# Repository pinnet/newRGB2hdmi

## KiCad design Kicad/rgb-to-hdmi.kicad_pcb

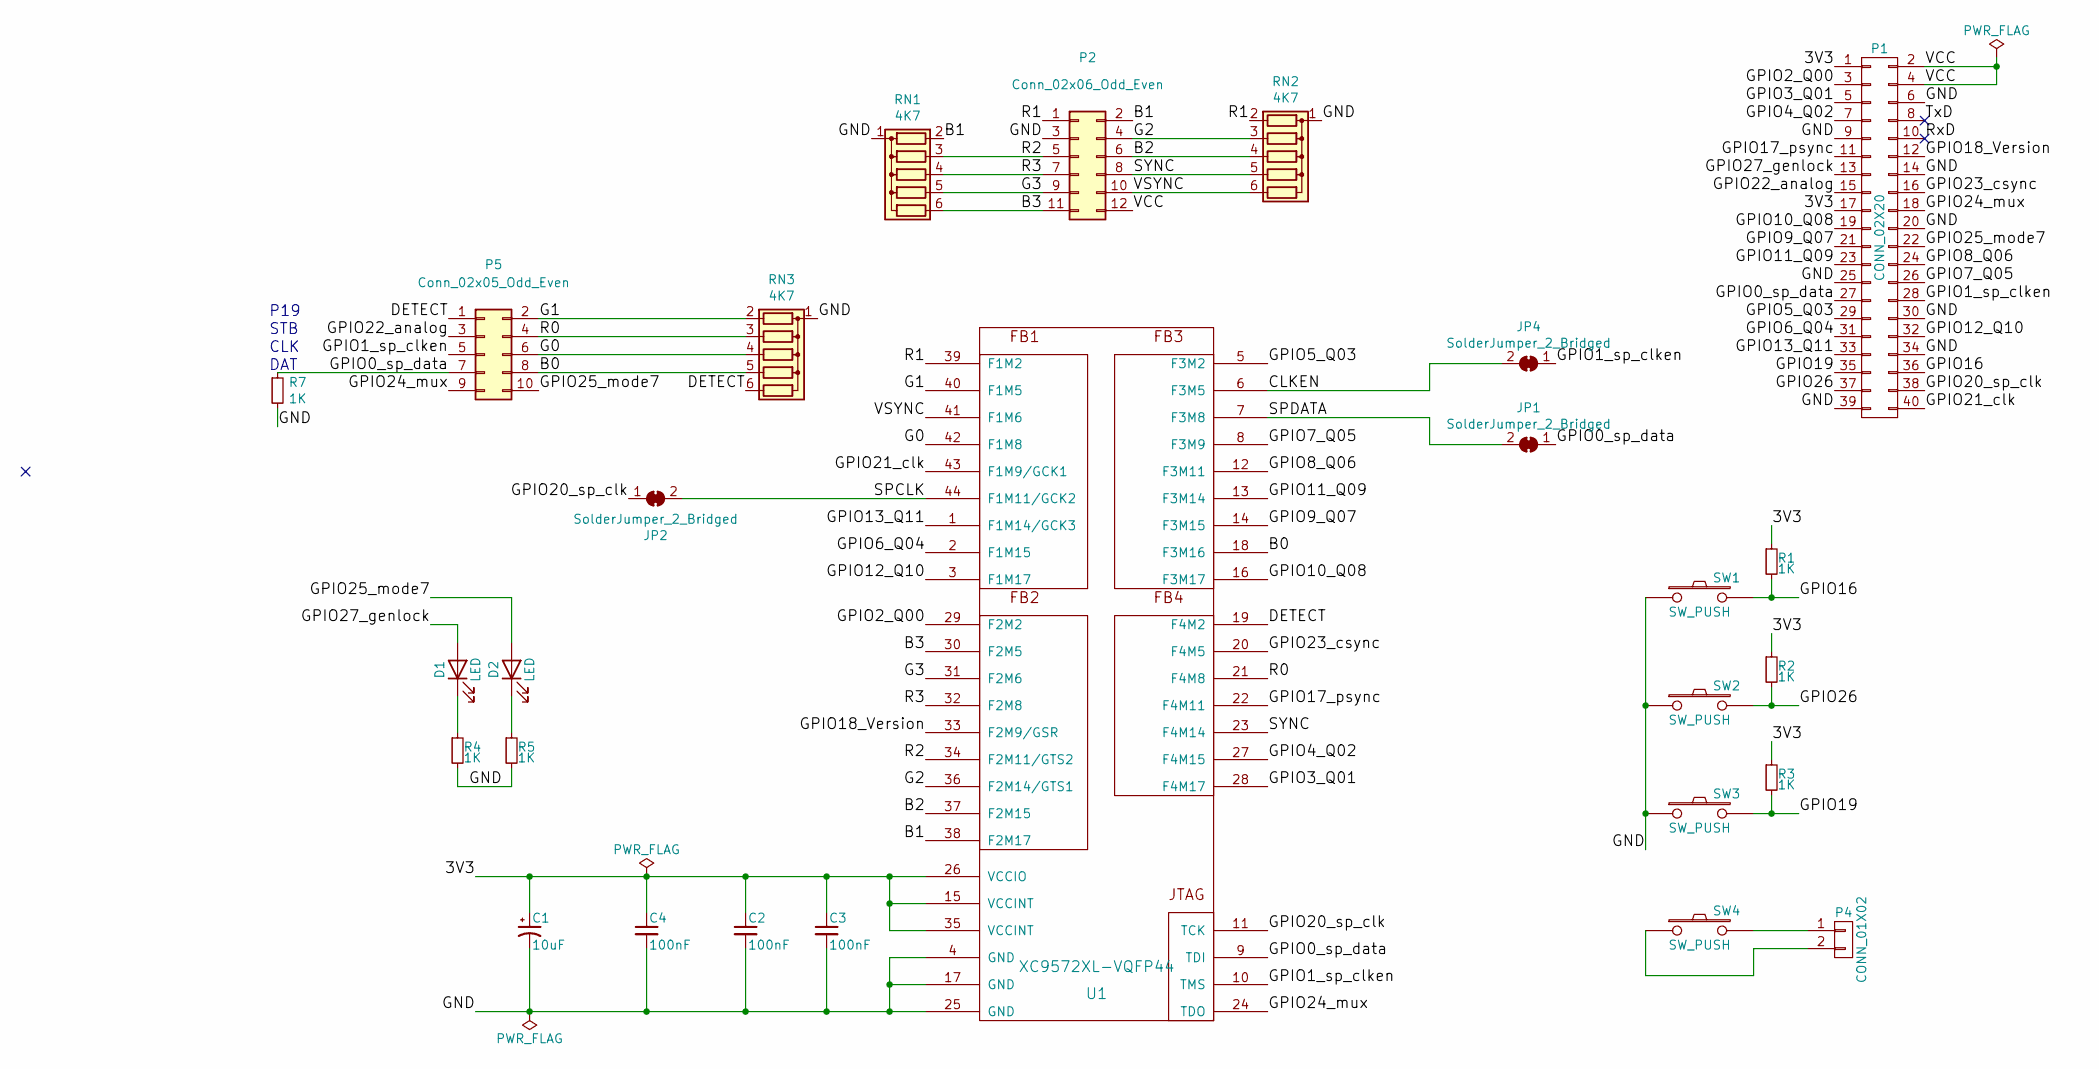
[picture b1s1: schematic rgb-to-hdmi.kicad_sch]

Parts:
C1: 10uF; C_0805_2012Metric_Pad1.15x1.40mm_HandSolder
C2, C3, C4: 100nF; C_0805_2012Metric_Pad1.15x1.40mm_HandSolder
D1, D2: LED; LED_D3.0mm
JP1, JP2, JP4: SolderJumper_2_Bridged; SolderJumper-2_P1.3mm_Bridged_RoundedPad1.0x1.5mm
P1: CONN_02X20; PinSocket_2x20_P2.54mm_Vertical_Custom
P2: Conn_02x06_Odd_Even; PinHeader_2x06_P2.54mm_Horizontal
P4: CONN_01X02; PinSocket_1x02_P2.54mm_Vertical_Custom
P5: Conn_02x05_Odd_Even; PinSocket_2x05_P2.54mm_Vertical
R1, R2, R3, R4, R5, R7: 1K; R_0805_2012Metric_Pad1.15x1.40mm_HandSolder
RN1, RN2, RN3: 4K7; R_Array_SIP6
SW1, SW2, SW3, SW4: SW_PUSH; SW_PUSH_6mm_H5mm
U1: XC9572XL-VQFP44; LQFP-44_10x10mm_P0.8mm

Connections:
/3V3: C1.1, C2.1, C3.1, C4.1, P1.1, P1.17, R1.1, R2.1, R3.1, U1.15 (VCCINT), U1.26 (VCCIO), U1.35 (VCCINT)
/B0: P5.8, RN3.5 (R4), U1.18 (F3M16)
/B1: P2.2, RN1.2 (R1), U1.38 (F2M17)
/B2: P2.6, RN2.4 (R3), U1.37 (F2M15)
/B3: P2.11, RN1.6 (R5), U1.30 (F2M5)
/CLKEN: JP4.2 (B), U1.6 (F3M5)
/DETECT: P5.1, RN3.6 (R5), U1.19 (F4M2)
/G0: P5.6, RN3.4 (R3), U1.42 (F1M8)
/G1: P5.2, RN3.2 (R1), U1.40 (F1M5)
/G2: P2.4, RN2.3 (R2), U1.36 (F2M14/GTS1)
/G3: P2.9, RN1.5 (R4), U1.31 (F2M6)
/GND: C1.2, C2.2, C3.2, C4.2, P1.6, P1.9, P1.14, P1.20, P1.25, P1.30, P1.34, P1.39, P2.3, R4.2, R5.2, R7.2, RN1.1 (common), RN2.1 (common), RN3.1 (common), SW1.1, SW2.1, SW3.1, U1.4 (GND), U1.17 (GND), U1.25 (GND)
/GPIO0_sp_data: JP1.1 (A), P1.27, P5.7, R7.1, U1.9 (TDI)
/GPIO1_sp_clken: JP4.1 (A), P1.28, P5.5, U1.10 (TMS)
/GPIO2_Q00: P1.3, U1.29 (F2M2)
/GPIO3_Q01: P1.5, U1.28 (F4M17)
/GPIO4_Q02: P1.7, U1.27 (F4M15)
/GPIO5_Q03: P1.29, U1.5 (F3M2)
/GPIO6_Q04: P1.31, U1.2 (F1M15)
/GPIO7_Q05: P1.26, U1.8 (F3M9)
/GPIO8_Q06: P1.24, U1.12 (F3M11)
/GPIO9_Q07: P1.21, U1.14 (F3M15)
/GPIO10_Q08: P1.19, U1.16 (F3M17)
/GPIO11_Q09: P1.23, U1.13 (F3M14)
/GPIO12_Q10: P1.32, U1.3 (F1M17)
/GPIO13_Q11: P1.33, U1.1 (F1M14/GCK3)
/GPIO16: P1.36, R1.2, SW1.2
/GPIO17_psync: P1.11, U1.22 (F4M11)
/GPIO18_Version: P1.12, U1.33 (F2M9/GSR)
/GPIO19: P1.35, R3.2, SW3.2
/GPIO20_sp_clk: JP2.1 (A), P1.38, U1.11 (TCK)
/GPIO21_clk: P1.40, U1.43 (F1M9/GCK1)
/GPIO22_analog: P1.15, P5.3
/GPIO23_csync: P1.16, U1.20 (F4M5)
/GPIO24_mux: P1.18, P5.9, U1.24 (TDO)
/GPIO25_mode7: D2.2 (A), P1.22, P5.10
/GPIO26: P1.37, R2.2, SW2.2
/GPIO27_genlock: D1.2 (A), P1.13
/R0: P5.4, RN3.3 (R2), U1.21 (F4M8)
/R1: P2.1, RN2.2 (R1), U1.39 (F1M2)
/R2: P2.5, RN1.3 (R2), U1.34 (F2M11/GTS2)
/R3: P2.7, RN1.4 (R3), U1.32 (F2M8)
/RxD: P1.10
/SPCLK: JP2.2 (B), U1.44 (F1M11/GCK2)
/SPDATA: JP1.2 (B), U1.7 (F3M8)
/SYNC: P2.8, RN2.5 (R4), U1.23 (F4M14)
/TxD: P1.8
/VCC: P1.2, P1.4, P2.12
/VSYNC: P2.10, RN2.6 (R5), U1.41 (F1M6)
unnamed: D1.1 (K), R4.1
unnamed: D2.1 (K), R5.1
unnamed: P4.1, SW4.2
unnamed: P4.2, SW4.1

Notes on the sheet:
DAT
CLK
STB
P19

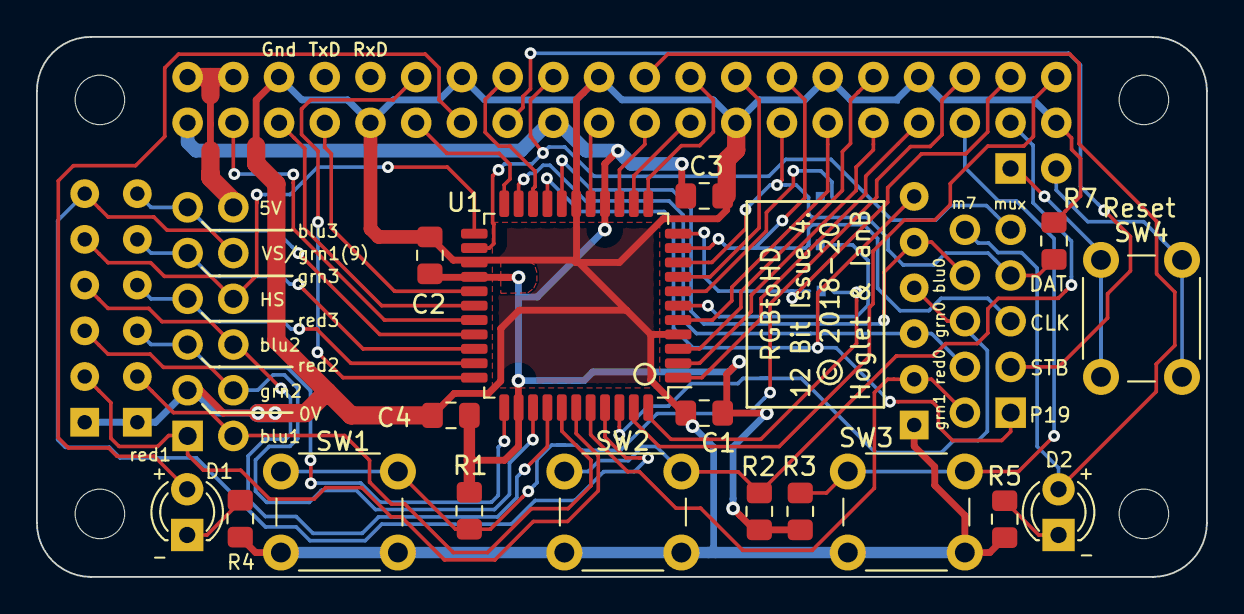
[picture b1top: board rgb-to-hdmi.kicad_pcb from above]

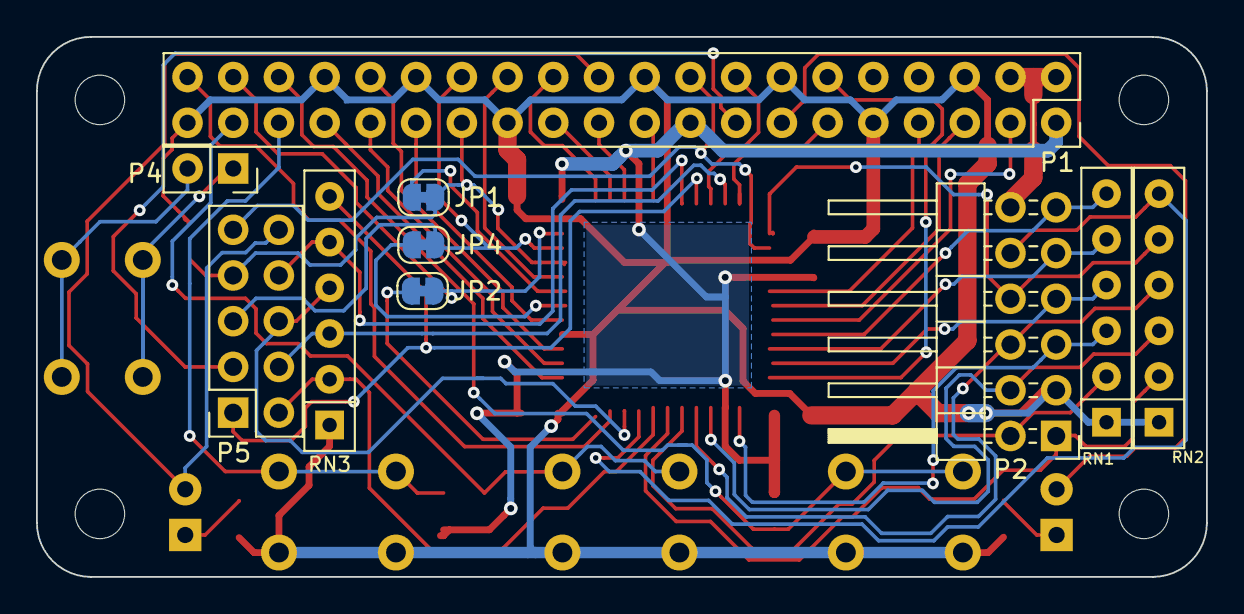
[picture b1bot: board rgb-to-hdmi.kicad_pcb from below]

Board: 2 copper layers, 65.0 x 30.0 mm, 27 parts (10 on the bottom side), 51 nets.

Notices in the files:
Kicad/rgb-to-hdmi.kicad_pcb:
© 2018-20
